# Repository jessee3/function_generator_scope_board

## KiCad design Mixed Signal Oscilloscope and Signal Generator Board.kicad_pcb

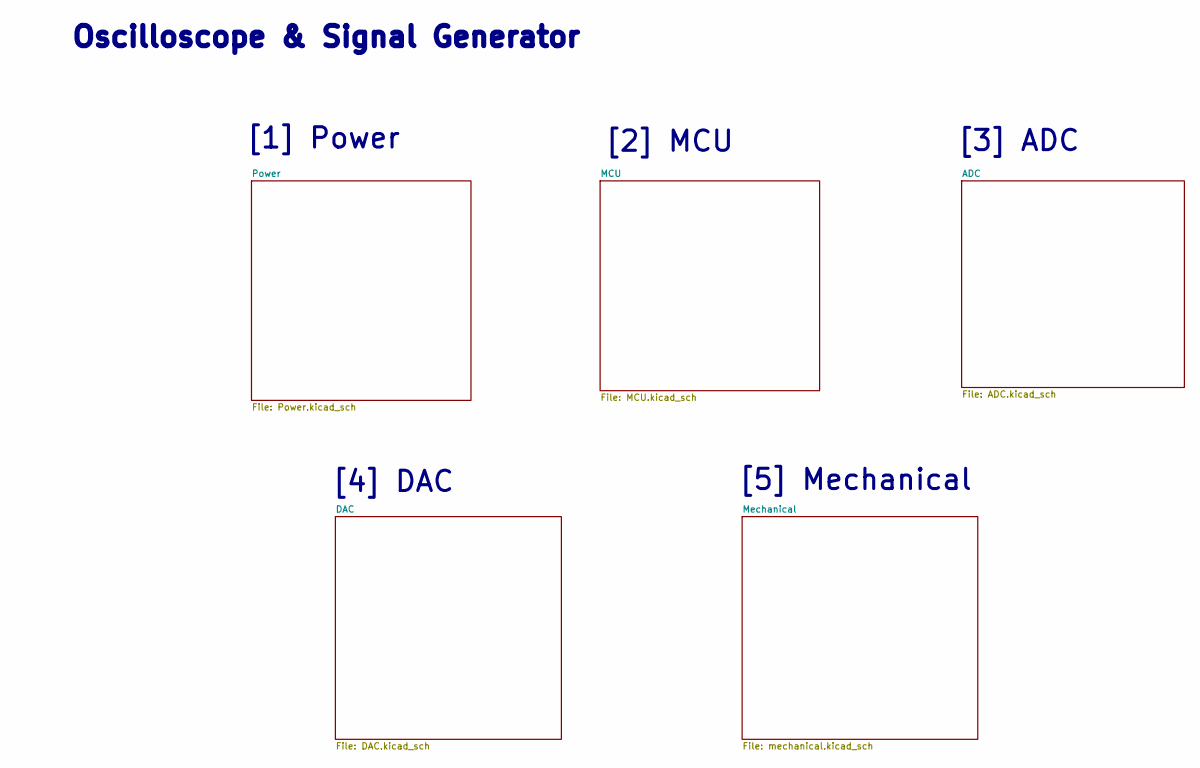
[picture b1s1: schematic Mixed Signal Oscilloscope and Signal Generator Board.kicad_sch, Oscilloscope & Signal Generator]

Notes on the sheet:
[1] Power
[3] ADC
Oscilloscope & Signal Generator
[4] DAC
[2] MCU
[5] Mechanical

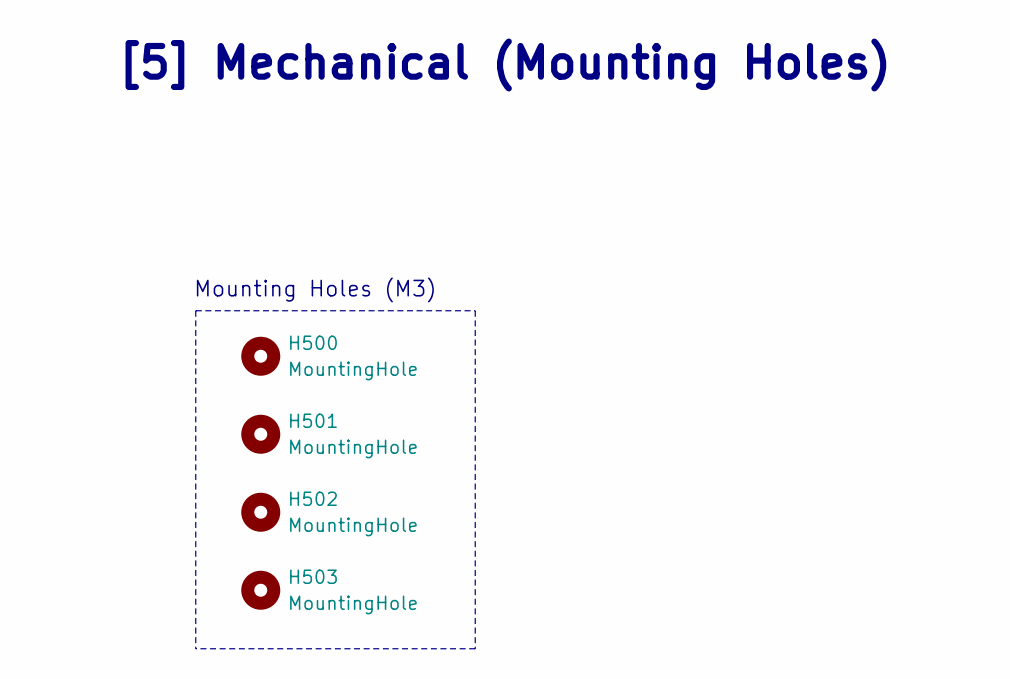
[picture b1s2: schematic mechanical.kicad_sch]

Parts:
H500, H501, H502, H503: MountingHole; MountingHole_3.2mm_M3

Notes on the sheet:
Mounting Holes (M3)
[5] Mechanical (Mounting Holes)

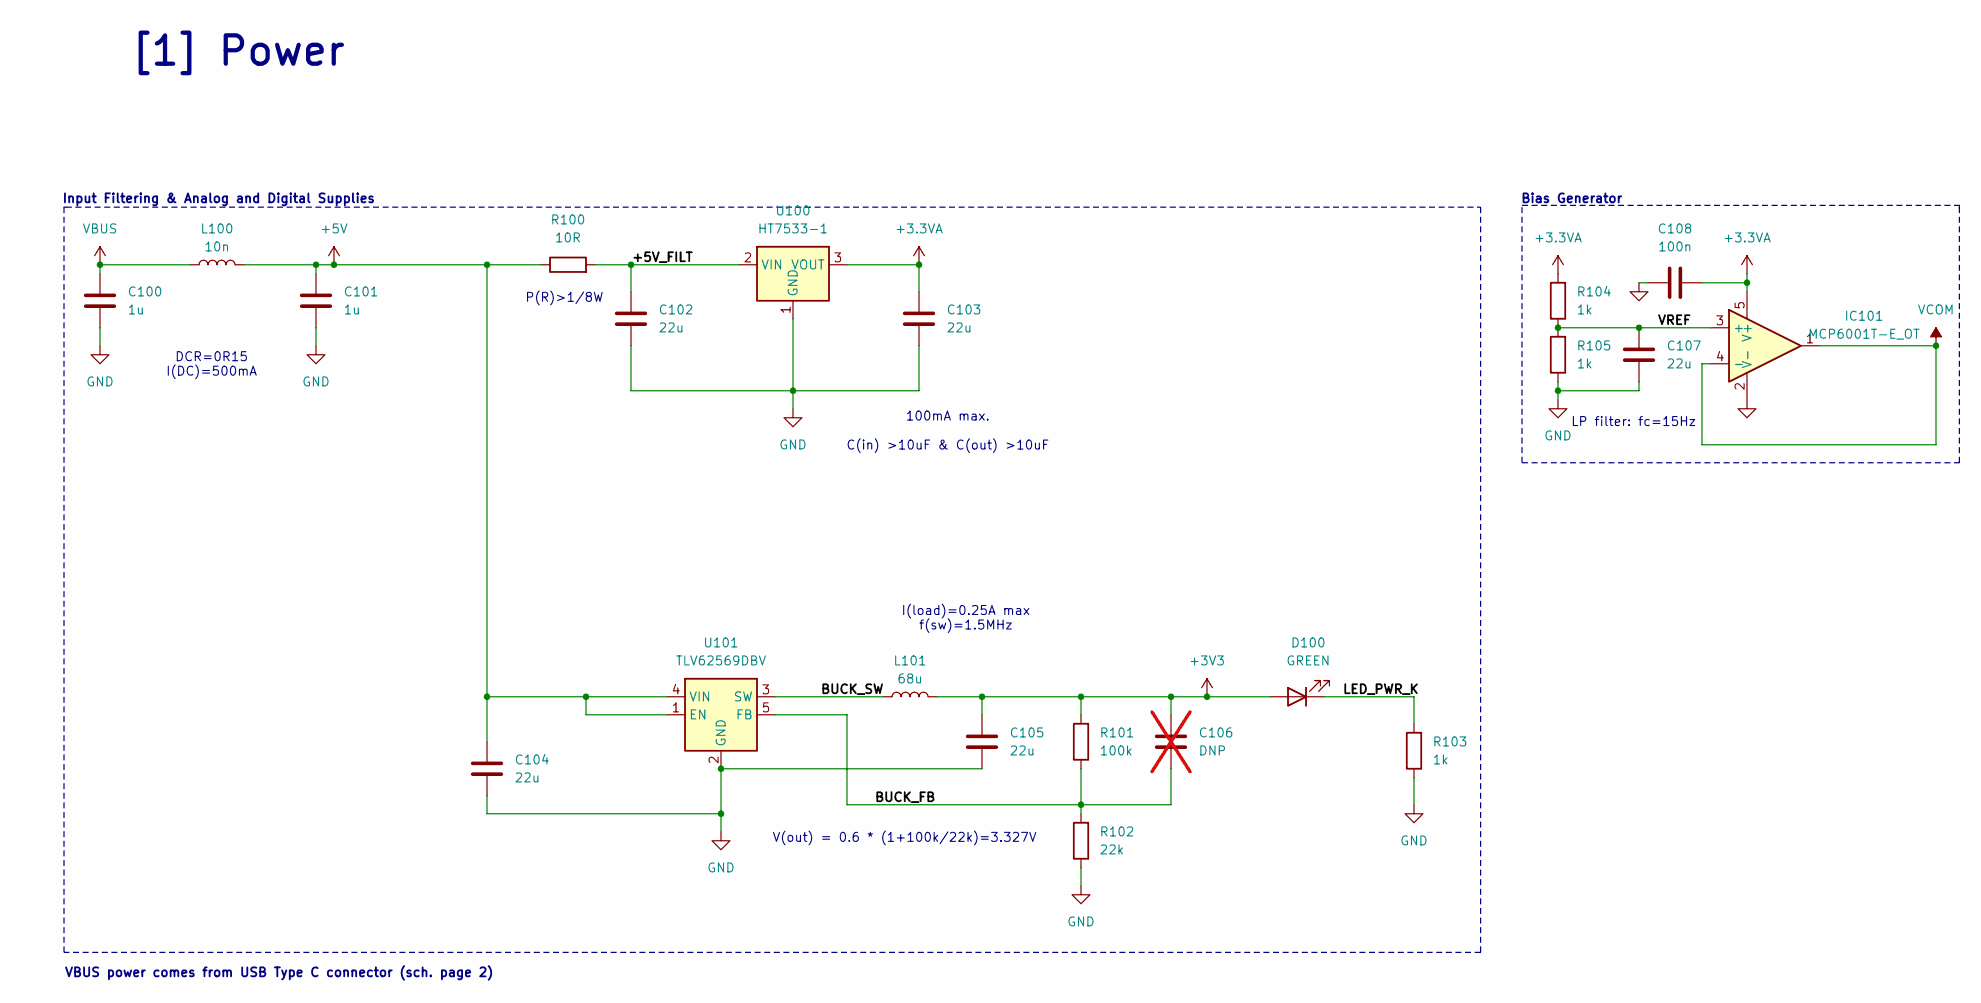
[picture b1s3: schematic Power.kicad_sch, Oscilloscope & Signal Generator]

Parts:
C100, C101: 1u; C_0603_1608Metric; Manufacturer_Part_Number CL10A105KO8NNNC; LCSC Part Number C1592
C102, C103, C104, C105, C107: 22u; C_0805_2012Metric; Manufacturer_Part_Number CL21A226MAQNNNE; LCSC Part Number C45783
C106: DNP; C_0402_1005Metric; not fitted
C108: 100n; C_0402_1005Metric; Manufacturer_Part_Number CL05B104KO5NNNC; LCSC Part Number C1525
D100: GREEN; LED_0603_1608Metric; Manufacturer_Part_Number LTST-C191KGKT; LCSC Part Number C125098
IC101: MCP6001T-E_OT; SOT95P270X145-5N; Manufacturer_Part_Number MCP6001T-E/OT; LCSC Part Number C29429
L100: 10n; L_0402_1005Metric; Manufacturer_Part_Number LQG15HS10NJ02D; LCSC Part Number C77103
L101: 68u; MWSA0603S; Manufacturer_Part_Number MWSA0603S-100MT
R100: 10R; R_0805_2012Metric; Manufacturer_Part_Number RC0805FR-0710RL; LCSC Part Number C96347
R101: 100k; R_0402_1005Metric; Manufacturer_Part_Number RC0402FR-07100KL; LCSC Part Number C60491
R102: 22k; R_0402_1005Metric; Manufacturer_Part_Number AECR0402F22K0K9; LCSC Part Number C328311
R103, R104, R105: 1k; R_0402_1005Metric; Manufacturer_Part_Number RC0402FR-071KL; LCSC Part Number C106235
U100: HT7533-1; SOT-89-3; Manufacturer_Part_Number HT7533-1; LCSC Part Number C5451672
U101: TLV62569DBV; SOT-23-5; Manufacturer_Part_Number TLV62569DBVR; LCSC Part Number C141836

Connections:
+3.3VA: C103.1, C108.2, IC101.5 (V+), R104.2, U100.3 (VOUT); also elsewhere on the board
+3V3: C105.1, C106.1, D100.2 (A), L101.2, R101.2; also elsewhere on the board
+5V: C101.1, C104.1, L100.2, R100.1, U101.1 (EN), U101.4 (VIN); also elsewhere on the board
/Power/+5V_FILT: C102.1, R100.2, U100.2 (VIN)
/Power/BUCK_FB: C106.2, R101.1, R102.2, U101.5 (FB)
/Power/BUCK_SW: L101.1, U101.3 (SW)
/Power/LED_PWR_K: D100.1 (K), R103.2
/Power/VREF: C107.1, IC101.3 (+), R104.1, R105.2
GND: C100.2, C101.2, C102.2, C103.2, C104.2, C105.2, C107.2, C108.1, IC101.2 (V-), R102.1, R103.1, R105.1, U100.1 (GND), U101.2 (GND); also elsewhere on the board
VBUS: C100.1, L100.1; also elsewhere on the board
VCOM: IC101.1, IC101.4 (-); also elsewhere on the board

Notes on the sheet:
Bias Generator
V(out) = 0.6 * (1+100k/22k)=3.327V
P(R)>1/8W
100mA max. C(in) >10uF & C(out) >10uF
Input Filtering & Analog and Digital Supplies
VBUS power comes from USB Type C connector (sch. page 2)
DCR=0R15 I(DC)=500mA
I(load)=0.25A max f(sw)=1.5MHz
LP filter: fc=15Hz
[1] Power

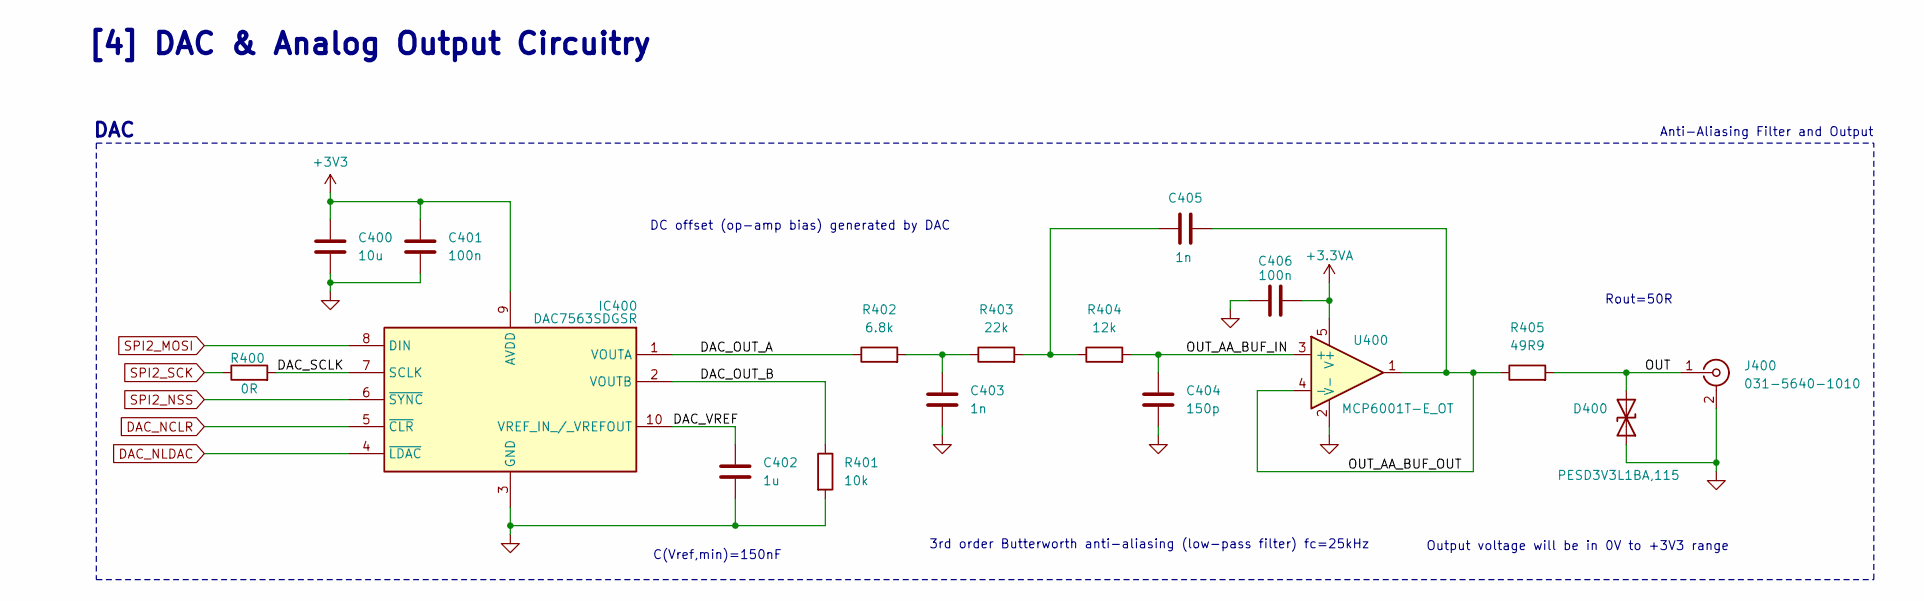
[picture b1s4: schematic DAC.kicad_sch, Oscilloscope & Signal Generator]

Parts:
C400: 10u; C_0603_1608Metric; Manufacturer_Part_Number CL10A106MQ8NNNC; LCSC Part Number C1691
C401, C406: 100n; C_0402_1005Metric; Manufacturer_Part_Number CL05B104KO5NNNC; LCSC Part Number C1525
C402: 1u; C_0603_1608Metric; Manufacturer_Part_Number CL10A105KO8NNNC; LCSC Part Number C1592
C403, C405: 1n; C_0402_1005Metric; Manufacturer_Part_Number CL05B102KB5NNNC; LCSC Part Number C14442
C404: 150p; C_0402_1005Metric; Manufacturer_Part_Number CL05C151JB51PNC; LCSC Part Number C472448
D400: PESD3V3L1BA,115; SOD2512X110N; Manufacturer_Part_Number PESD3V3L1BA,115; LCSC Part Number C51450
IC400: DAC7563SDGSR; SOP50P490X110-10N; Manufacturer_Part_Number DAC7563SDGSR; LCSC Part Number C601656
J400: 031-5640-1010; AMPHENOL-BNC-031-5640-1010; Manufacturer_Part_Number 31-5640-1010; LCSC Part Number C6997605
R400: 0R; R_0402_1005Metric; Manufacturer_Part_Number RC0402FR-070RL; LCSC Part Number C106231
R401: 10k; R_0402_1005Metric; Manufacturer_Part_Number RC0402FR-0710KL; LCSC Part Number C60490
R402: 6.8k; R_0402_1005Metric; Manufacturer_Part_Number RC0402JR-076K8L; LCSC Part Number C137847
R403: 22k; R_0402_1005Metric; Manufacturer_Part_Number AECR0402F22K0K9; LCSC Part Number C328311
R404: 12k; R_0402_1005Metric; Manufacturer_Part_Number FRC0402J123 TS; LCSC Part Number C2906889
R405: 49R9; R_0402_1005Metric; Manufacturer_Part_Number RC0402FR-0749R9L; LCSC Part Number C87044
U400: MCP6001T-E_OT; SOT95P270X145-5N; Manufacturer_Part_Number MCP6001T-E/OT; LCSC Part Number C29429

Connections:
+3.3VA: C406.2, U400.5 (V+); also elsewhere on the board
+3V3: C400.1, C401.1, IC400.9 (AVDD); also elsewhere on the board
/DAC/DAC_OUT_A: IC400.1 (VOUTA), R402.1
/DAC/DAC_OUT_B: IC400.2 (VOUTB), R401.1
/DAC/DAC_SCLK: IC400.7 (SCLK), R400.2
/DAC/DAC_VREF: C402.1, IC400.10 (VREF_IN_/_VREFOUT)
/DAC/OUT: D400.2 (A2), J400.1 (In), R405.2
/DAC/OUT_AA_BUF_IN: C404.1, R404.2, U400.3 (+)
/DAC/OUT_AA_BUF_OUT: C405.2, R405.1, U400.1, U400.4 (-)
DAC_NCLR: IC400.5 (~CLR); also elsewhere on the board
DAC_NLDAC: IC400.4 (~LDAC); also elsewhere on the board
GND: C400.2, C401.2, C402.2, C403.2, C404.2, C406.1, D400.1 (A1), IC400.3 (GND), J400.2 (Ext), R401.2, U400.2 (V-); also elsewhere on the board
unnamed: C403.1, R402.2, R403.1
unnamed: C405.1, R403.2, R404.1
SPI2_MOSI: IC400.8 (DIN); also elsewhere on the board
SPI2_NSS: IC400.6 (~SYNC); also elsewhere on the board
SPI2_SCK: R400.1; also elsewhere on the board

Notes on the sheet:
3rd order Butterworth anti-aliasing (low-pass filter) fc=25kHz
C(Vref,min)=150nF
Output voltage will be in 0V to +3V3 range
[4] DAC & Analog Output Circuitry
Rout=50R
DAC
Anti-Aliasing Filter and Output
DC offset (op-amp bias) generated by DAC

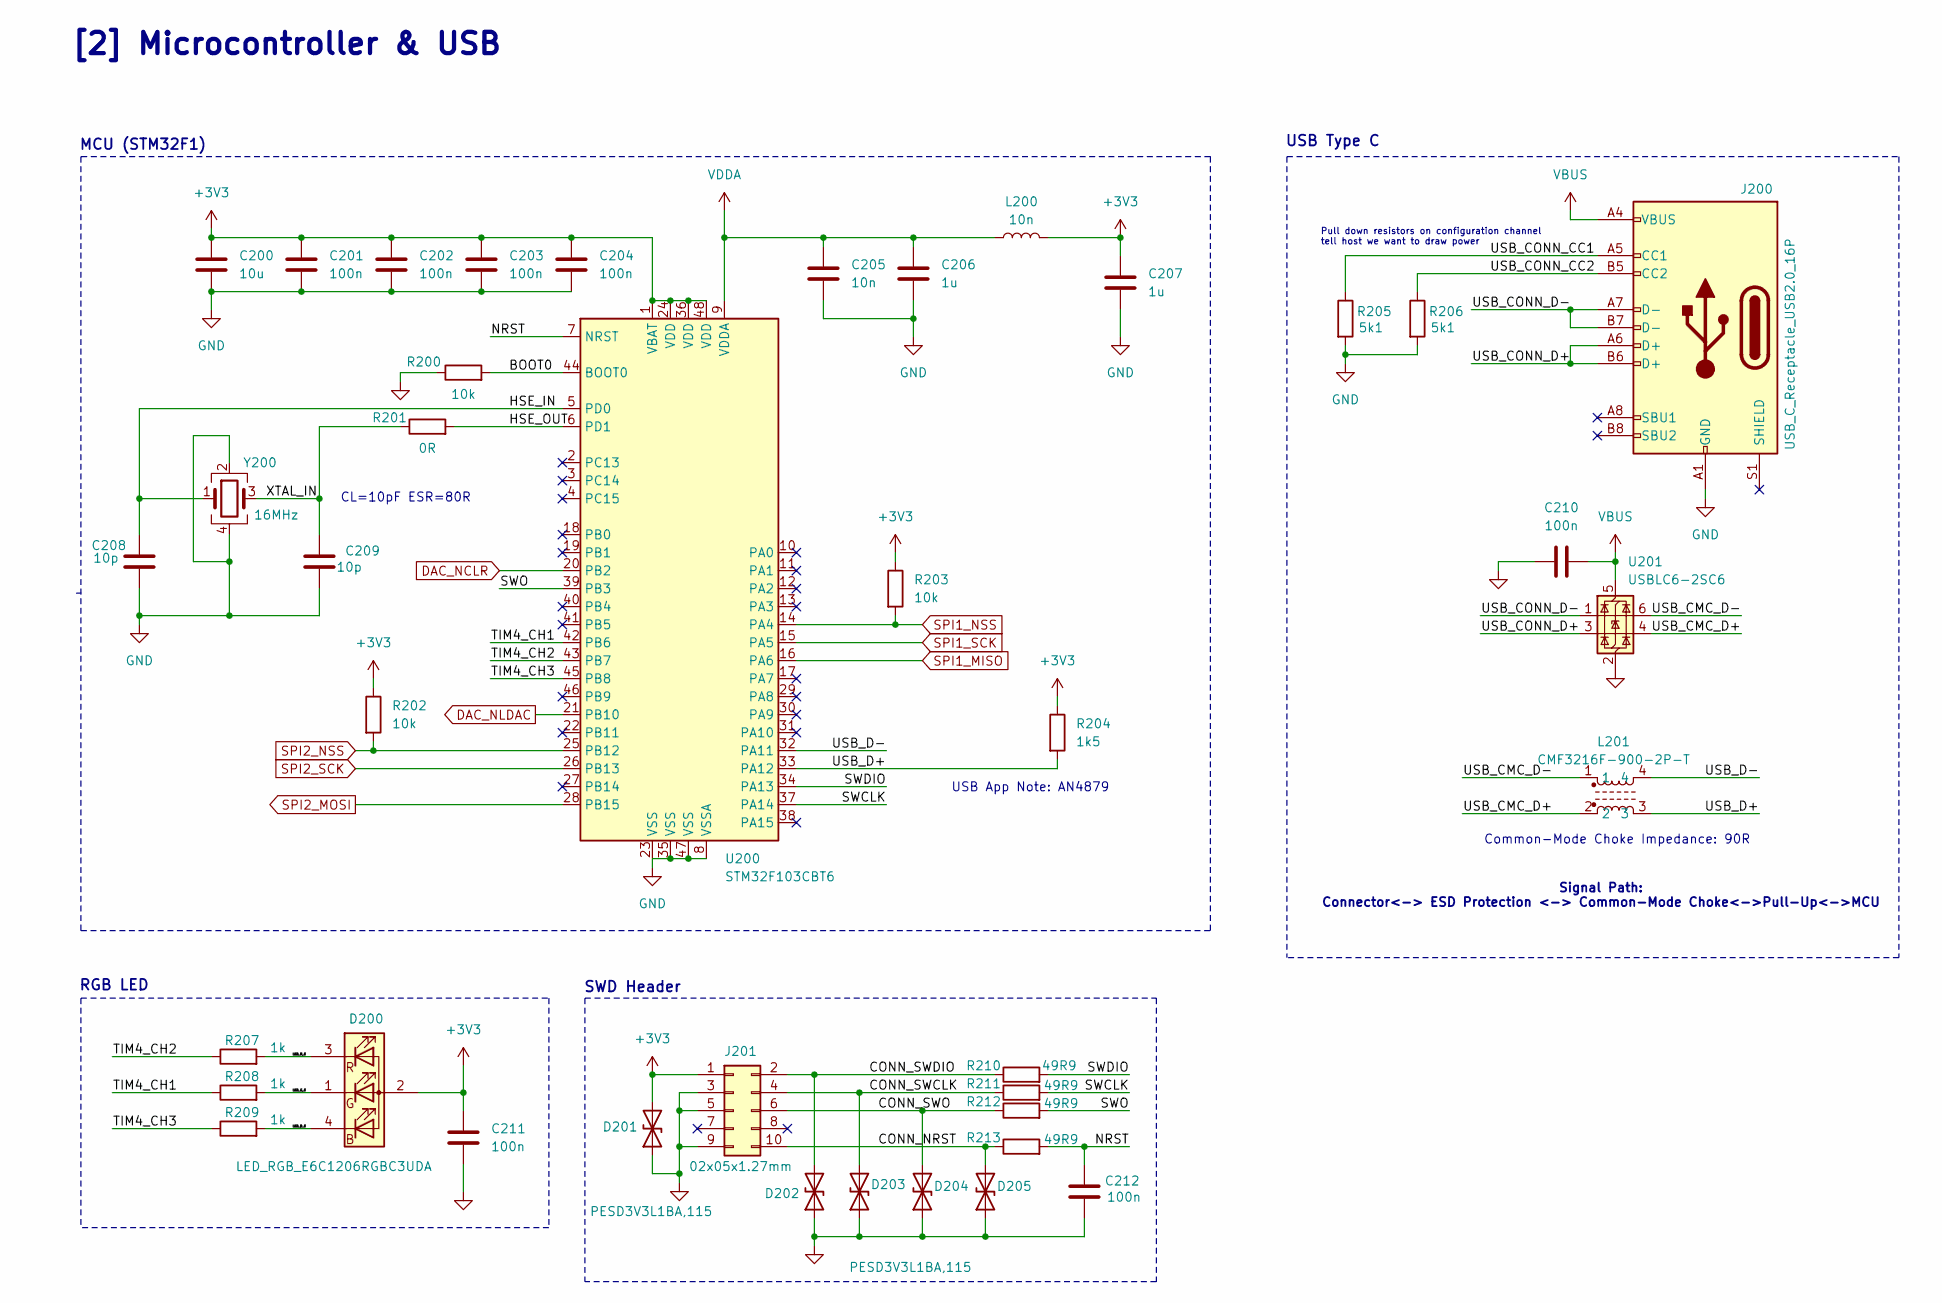
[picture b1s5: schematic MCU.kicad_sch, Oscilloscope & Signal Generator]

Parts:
C200: 10u; C_0603_1608Metric; Manufacturer_Part_Number CL10A106MQ8NNNC; LCSC Part Number C1691
C201, C202, C203, C204, C210, C211, C212: 100n; C_0402_1005Metric; Manufacturer_Part_Number CL05B104KO5NNNC; LCSC Part Number C1525
C205: 10n; C_0402_1005Metric; Manufacturer_Part_Number CL05B103KB5NNNC; LCSC Part Number C15195
C206, C207: 1u; C_0603_1608Metric; Manufacturer_Part_Number CL10A105KO8NNNC; LCSC Part Number C1592
C208, C209: 10p; C_0402_1005Metric; Manufacturer_Part_Number CL05C100JB5NNNC; LCSC Part Number C32949
D200: LED_RGB_E6C1206RGBC3UDA; E6C1206RGBC3UDA; Manufacturer_Part_Number E6C1206RGBC3UDA; LCSC Part Number C375571
D201, D202, D203, D204, D205: PESD3V3L1BA,115; SOD2512X110N; Manufacturer_Part_Number PESD3V3L1BA,115; LCSC Part Number C51450
J200: USB_C_Receptacle_USB2.0_16P; USB_C_Receptacle_HRO_TYPE-C-31-M-12; Manufacturer_Part_Number TYPEC-304A-ACP16G; LCSC Part Number C2909608
J201: 02x05x1.27mm; PinHeader_2x05_P1.27mm_Vertical_SMD; Manufacturer_Part_Number ZX-PZ1.27-2-5PZZ; LCSC Part Number C7501289
L200: 10n; L_0402_1005Metric; Manufacturer_Part_Number LQG15HS10NJ02D; LCSC Part Number C77103
L201: CMF3216F-900-2P-T; CMC-1206; Manufacturer_Part_Number CMF3216F-900-2P-T; LCSC Part Number C963740
R200, R202, R203: 10k; R_0402_1005Metric; Manufacturer_Part_Number RC0402FR-0710KL; LCSC Part Number C60490
R201: 0R; R_0402_1005Metric; Manufacturer_Part_Number RC0402FR-070RL; LCSC Part Number C106231
R204: 1k5; R_0402_1005Metric; Manufacturer_Part_Number AS02FTE1501; LCSC Part Number C409724
R205, R206: 5k1; R_0402_1005Metric; Manufacturer_Part_Number CR-02FL6---5K1; LCSC Part Number C409700
R207, R208, R209: 1k; R_0402_1005Metric; Manufacturer_Part_Number RC0402FR-071KL; LCSC Part Number C106235
R210, R211, R212, R213: 49R9; R_0402_1005Metric; Manufacturer_Part_Number RC0402FR-0749R9L; LCSC Part Number C87044
U200: STM32F103CBT6; LQFP-48_7x7mm_P0.5mm; Manufacturer_Part_Number STM32F103CBT6; LCSC Part Number C8304
U201: USBLC6-2SC6; SOT-23-6; Manufacturer_Part_Number USBLC6-2SC6; LCSC Part Number C7519
Y200: 16MHz; Crystal_SMD_3225-4Pin_3.2x2.5mm; Manufacturer_Part_Number HY16MSMD3225DB1R30; LCSC Part Number SMD3225-4P

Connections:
+3V3: C200.1, C201.1, C202.1, C203.1, C204.1, C207.1, C211.1, D200.2, D201.2 (A2), J201.1, L200.2, R202.1, R203.1, R204.1, U200.1 (VBAT), U200.24 (VDD), U200.36 (VDD), U200.48 (VDD); also elsewhere on the board
/MCU/BOOT0: R200.2, U200.44 (BOOT0)
/MCU/CONN_NRST: D205.2 (A2), J201.10, R213.1
/MCU/CONN_SWCLK: D203.2 (A2), J201.4, R211.1
/MCU/CONN_SWDIO: D202.2 (A2), J201.2, R210.1
/MCU/CONN_SWO: D204.2 (A2), J201.6, R212.1
/MCU/HSE_IN: C208.1, U200.5 (PD0), Y200.1
/MCU/HSE_OUT: R201.2, U200.6 (PD1)
/MCU/LED_B_K: D200.4, R209.2
/MCU/LED_G_K: D200.1, R208.2
/MCU/LED_R_K: D200.3, R207.2
/MCU/NRST: C212.2, R213.2, U200.7 (NRST)
/MCU/SWCLK: R211.2, U200.37 (PA14)
/MCU/SWDIO: R210.2, U200.34 (PA13)
/MCU/SWO: R212.2, U200.39 (PB3)
/MCU/TIM4_CH1: R208.1, U200.42 (PB6)
/MCU/TIM4_CH2: R207.1, U200.43 (PB7)
/MCU/TIM4_CH3: R209.1, U200.45 (PB8)
/MCU/USB_CMC_D+: L201.2, U201.4 (I/O2)
/MCU/USB_CMC_D-: L201.1, U201.6 (I/O1)
/MCU/USB_CONN_CC1: J200.A5 (CC1), R205.1
/MCU/USB_CONN_CC2: J200.B5 (CC2), R206.1
/MCU/USB_CONN_D+: J200.A6 (D+), J200.B6 (D+), U201.3 (I/O2)
/MCU/USB_CONN_D-: J200.A7 (D-), J200.B7 (D-), U201.1 (I/O1)
/MCU/USB_D+: L201.3, R204.2, U200.33 (PA12)
/MCU/USB_D-: L201.4, U200.32 (PA11)
/MCU/XTAL_IN: C209.1, R201.1, Y200.3
DAC_NCLR: U200.20 (PB2); also elsewhere on the board
DAC_NLDAC: U200.21 (PB10); also elsewhere on the board
GND: C200.2, C201.2, C202.2, C203.2, C204.2, C205.2, C206.2, C207.2, C208.2, C209.2, C210.1, C211.2, C212.1, D201.1 (A1), D202.1 (A1), D203.1 (A1), D204.1 (A1), D205.1 (A1), J200.A1 (GND), J200.A12 (GND), J200.B1 (GND), J200.B12 (GND), J201.3, J201.5, J201.9, R200.1, R205.2, R206.2, U200.8 (VSSA), U200.23 (VSS), U200.35 (VSS), U200.47 (VSS), U201.2 (GND), Y200.2, Y200.4; also elsewhere on the board
SPI1_MISO: U200.16 (PA6); also elsewhere on the board
SPI1_NSS: R203.2, U200.14 (PA4); also elsewhere on the board
SPI1_SCK: U200.15 (PA5); also elsewhere on the board
SPI2_MOSI: U200.28 (PB15); also elsewhere on the board
SPI2_NSS: R202.2, U200.25 (PB12); also elsewhere on the board
SPI2_SCK: U200.26 (PB13); also elsewhere on the board
VBUS: C210.2, J200.A4 (VBUS), J200.A9 (VBUS), J200.B4 (VBUS), J200.B9 (VBUS), U201.5 (VBUS); also elsewhere on the board
VDDA: C205.1, C206.1, L200.1, U200.9 (VDDA)

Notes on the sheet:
USB Type C
USB App Note: AN4879
[2] Microcontroller & USB
RGB LED
Signal Path: Connector<-> ESD Protection <-> Common-Mode Choke<->Pull-Up<->MCU
CL=10pF ESR=80R
MCU (STM32F1)
Pull down resistors on configuration channel tell host we want to draw power
Common-Mode Choke Impedance: 90R
SWD Header

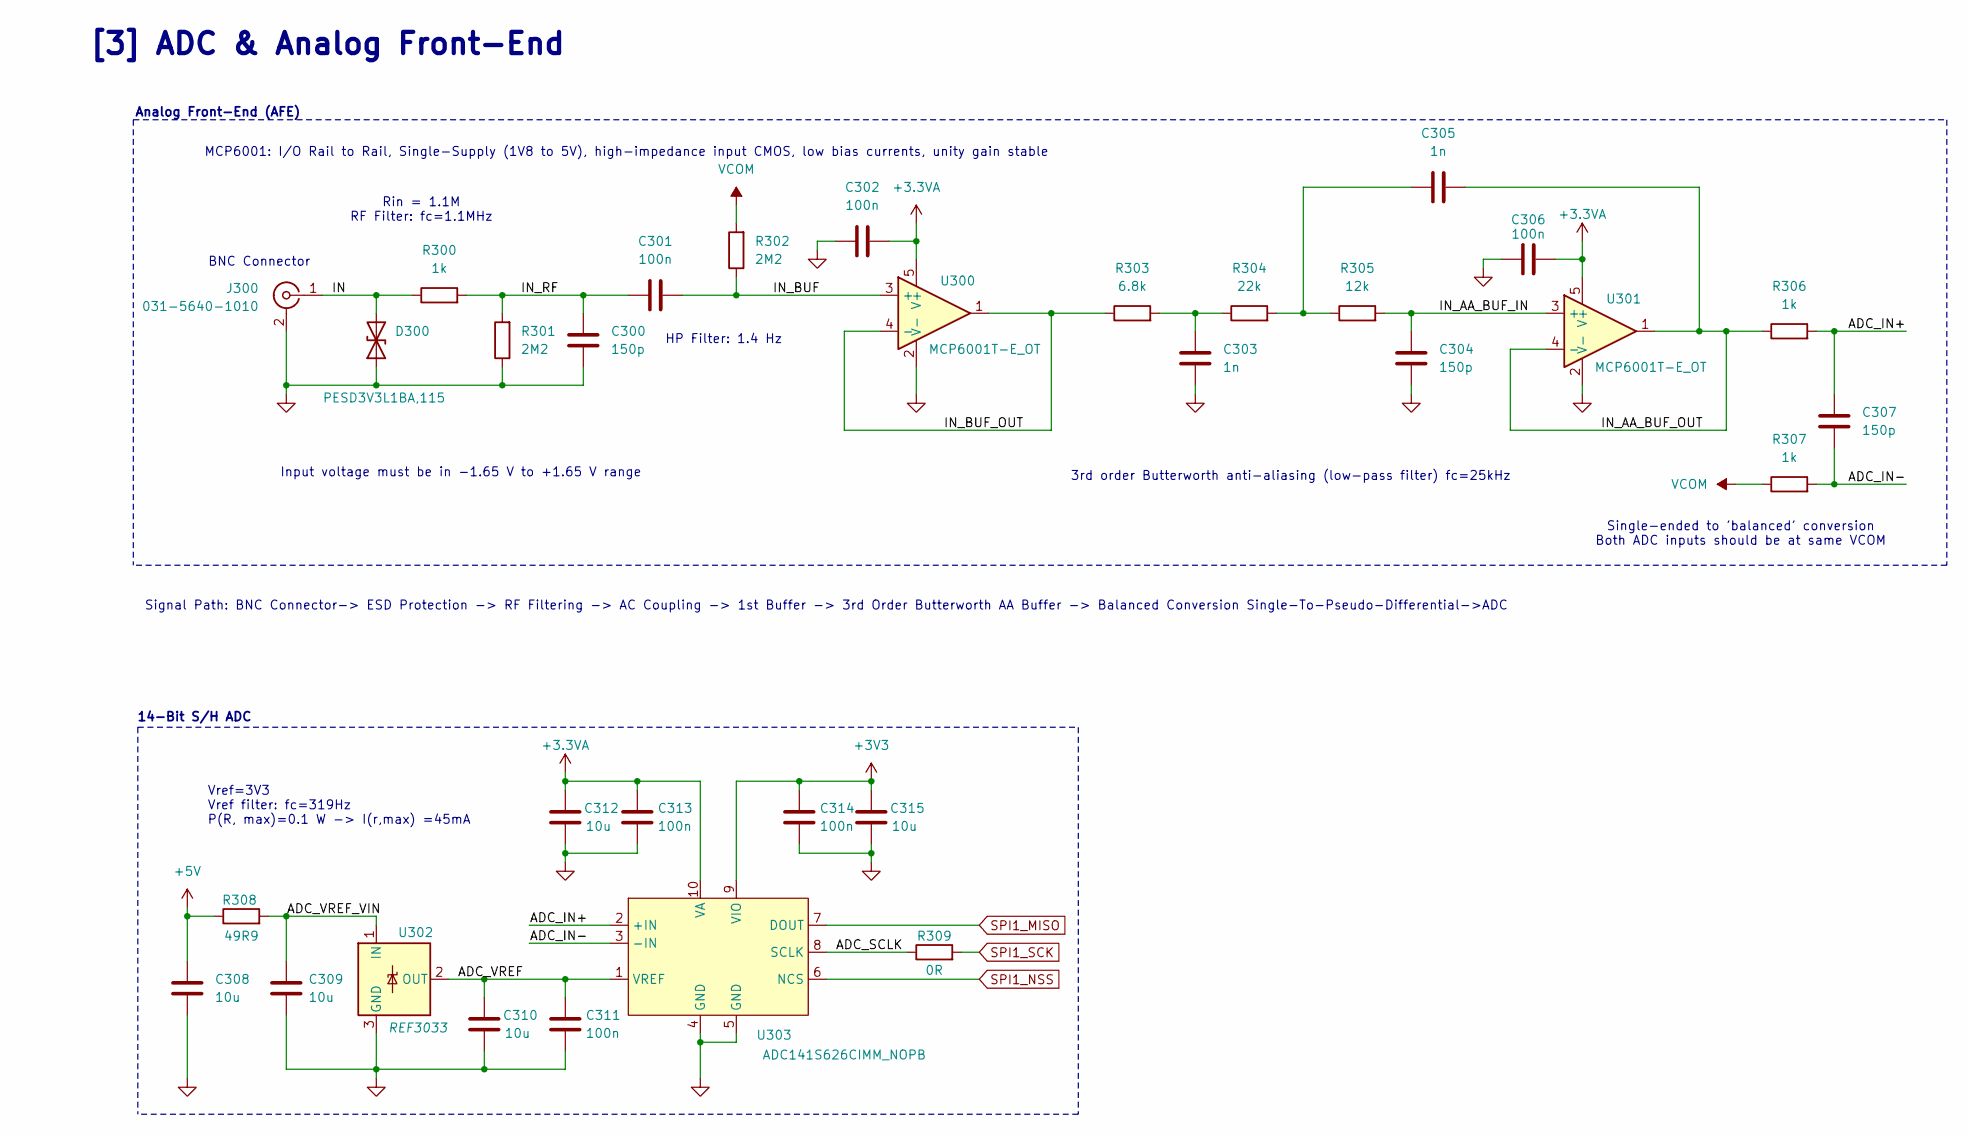
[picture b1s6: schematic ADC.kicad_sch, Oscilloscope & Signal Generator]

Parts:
C300, C304, C307: 150p; C_0402_1005Metric; Manufacturer_Part_Number CL05C151JB51PNC; LCSC Part Number C472448
C301, C302, C306, C311, C313, C314: 100n; C_0402_1005Metric; Manufacturer_Part_Number CL05B104KO5NNNC; LCSC Part Number C1525
C303, C305: 1n; C_0402_1005Metric; Manufacturer_Part_Number CL05B102KB5NNNC; LCSC Part Number C14442
C308, C309, C310, C312, C315: 10u; C_0603_1608Metric; Manufacturer_Part_Number CL10A106MQ8NNNC; LCSC Part Number C1691
D300: PESD3V3L1BA,115; SOD2512X110N; Manufacturer_Part_Number PESD3V3L1BA,115; LCSC Part Number C51450
J300: 031-5640-1010; AMPHENOL-BNC-031-5640-1010; Manufacturer_Part_Number 31-5640-1010; LCSC Part Number C6997605
R300, R306, R307: 1k; R_0402_1005Metric; Manufacturer_Part_Number RC0402FR-071KL; LCSC Part Number C106235
R301, R302: 2M2; R_0402_1005Metric; Manufacturer_Part_Number RC0402JR-072M2L; LCSC Part Number C274901
R303: 6.8k; R_0402_1005Metric; Manufacturer_Part_Number RC0402JR-076K8L; LCSC Part Number C137847
R304: 22k; R_0402_1005Metric; Manufacturer_Part_Number AECR0402F22K0K9; LCSC Part Number C328311
R305: 12k; R_0402_1005Metric; Manufacturer_Part_Number FRC0402J123 TS; LCSC Part Number C2906889
R308: 49R9; R_0402_1005Metric; Manufacturer_Part_Number RC0402FR-0749R9L; LCSC Part Number C87044
R309: 0R; R_0402_1005Metric; Manufacturer_Part_Number RC0402FR-070RL; LCSC Part Number C106231
U300, U301: MCP6001T-E_OT; SOT95P270X145-5N; Manufacturer_Part_Number MCP6001T-E/OT; LCSC Part Number C29429
U302: REF3033; SOT-23; Manufacturer_Part_Number View marketplace suppliers’ inventory i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; LCSC Part Number C36658
U303: ADC141S626CIMM_NOPB; SOP50P490X110-10N; Manufacturer_Part_Number ADC141S626CIMMX/NOPB; LCSC Part Number C2861039

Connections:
+3.3VA: C302.2, C306.2, C312.1, C313.1, U300.5 (V+), U301.5 (V+), U303.10 (VA); also elsewhere on the board
+3V3: C314.1, C315.1, U303.9 (VIO); also elsewhere on the board
+5V: C308.1, R308.1; also elsewhere on the board
/ADC/ADC_IN+: C307.1, R306.2, U303.2 (+IN)
/ADC/ADC_IN-: C307.2, R307.2, U303.3 (-IN)
/ADC/ADC_SCLK: R309.1, U303.8 (SCLK)
/ADC/ADC_VREF: C310.1, C311.1, U302.2 (OUT), U303.1 (VREF)
/ADC/ADC_VREF_VIN: C309.1, R308.2, U302.1 (IN)
/ADC/IN: D300.2 (A2), J300.1 (In), R300.1
/ADC/IN_AA_BUF_IN: C304.1, R305.2, U301.3 (+)
/ADC/IN_AA_BUF_OUT: C305.2, R306.1, U301.1, U301.4 (-)
/ADC/IN_BUF: C301.2, R302.1, U300.3 (+)
/ADC/IN_BUF_OUT: R303.1, U300.1, U300.4 (-)
/ADC/IN_RF: C300.1, C301.1, R300.2, R301.2
GND: C300.2, C302.1, C303.2, C304.2, C306.1, C308.2, C309.2, C310.2, C311.2, C312.2, C313.2, C314.2, C315.2, D300.1 (A1), J300.2 (Ext), R301.1, U300.2 (V-), U301.2 (V-), U302.3 (GND), U303.4 (GND), U303.5 (GND); also elsewhere on the board
unnamed: C303.1, R303.2, R304.1
unnamed: C305.1, R304.2, R305.1
SPI1_MISO: U303.7 (DOUT); also elsewhere on the board
SPI1_NSS: U303.6 (NCS); also elsewhere on the board
SPI1_SCK: R309.2; also elsewhere on the board
VCOM: R302.2, R307.1; also elsewhere on the board

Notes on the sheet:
Analog Front-End (AFE)
Vref=3V3 Vref filter: fc=319Hz P(R, max)=0.1 W -> I(r,max) =45mA
[3] ADC & Analog Front-End
Rin = 1.1M RF Filter: fc=1.1MHz
Single-ended to 'balanced' conversion Both ADC inputs should be at same VCOM
HP Filter: 1.4 Hz
Signal Path: BNC Connector-> ESD Protection -> RF Filtering -> AC Coupling -> 1st Buffer -> 3rd Order Butterworth AA Buffer -> Balanced Conversion Single-To-Pseudo-Differential->ADC
3rd order Butterworth anti-aliasing (low-pass filter) fc=25kHz
14-Bit S/H ADC
BNC Connector
MCP6001: I/O Rail to Rail, Single-Supply (1V8 to 5V), high-impedance input CMOS, low bias currents, unity gain stable
Input voltage must be in -1.65 V to +1.65 V range

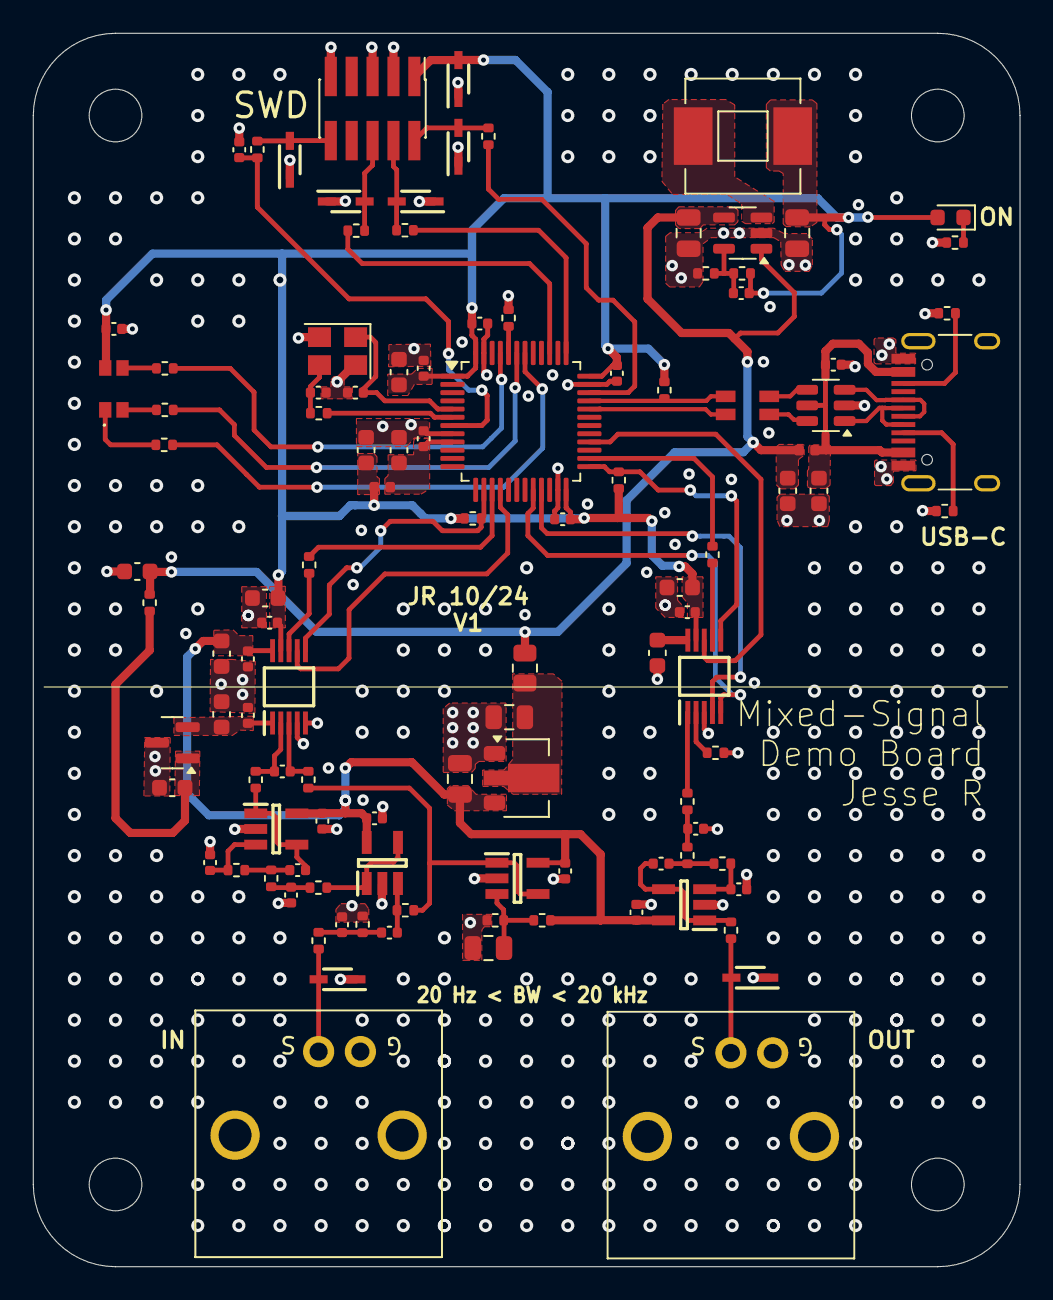
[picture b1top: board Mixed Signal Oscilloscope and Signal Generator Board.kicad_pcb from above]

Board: 4 copper layers, 60.0 x 75.0 mm, 114 parts (0 on the bottom side), 68 nets.
